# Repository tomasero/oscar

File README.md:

#Oscar
####Interactive Trashcan

---

###Sensors
- Infrared distance sensor
- Passive infrared sensor (motion detection)

###Actuators
- LEDs
- Sound

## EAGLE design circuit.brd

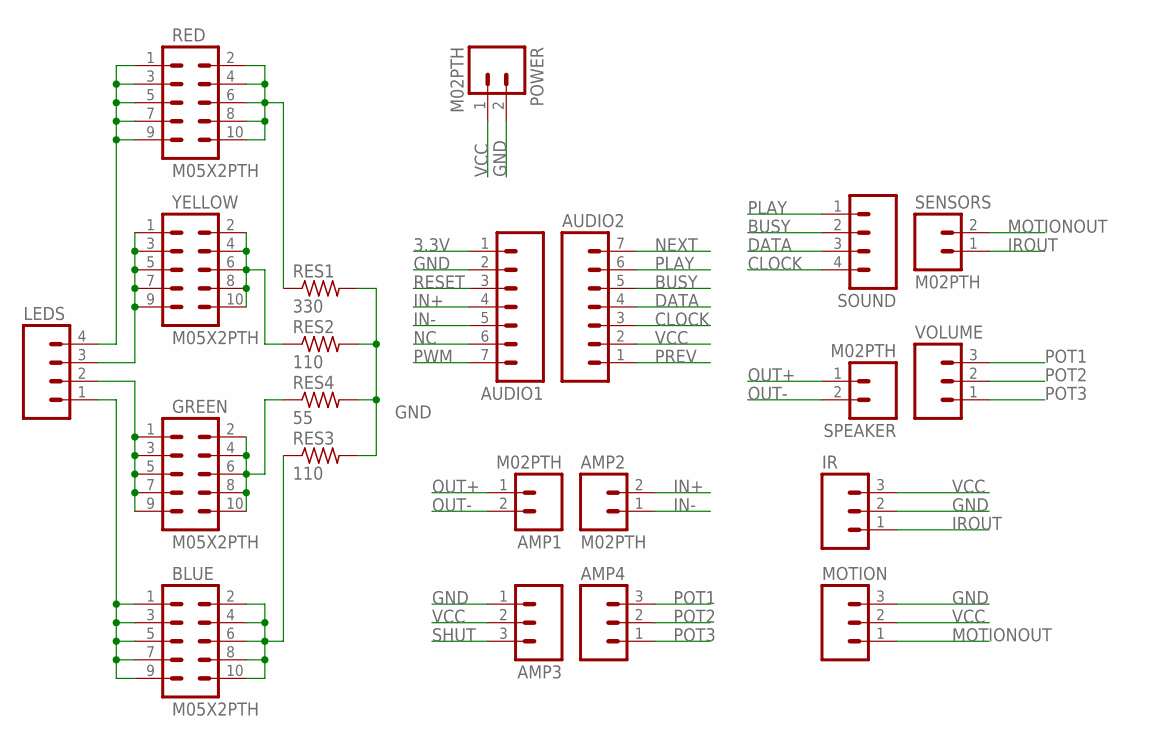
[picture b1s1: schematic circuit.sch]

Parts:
AMP1, AMP2: M02PTH; 1X02
AMP3, AMP4: M03PTH; 1X03
AUDIO1, AUDIO2: M07; 1X07
BLUE: M05X2PTH; AVR_ICSP
GREEN: M05X2PTH; AVR_ICSP
IR: M03PTH; 1X03
LEDS: M04PTH; 1X04
MOTION: M03PTH; 1X03
POWER: M02PTH; 1X02
RED: M05X2PTH; AVR_ICSP
RES1: 330; 0204V
RES2, RES3: 110; 0204V
RES4: 55; 0204V
SENSORS: M02PTH; 1X02
SOUND: M04PTH; 1X04
SPEAKER: M02PTH; 1X02
VOLUME: M03PTH; 1X03
YELLOW: M05X2PTH; AVR_ICSP

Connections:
3.3V: AUDIO1.1
BUSY: AUDIO2.5, SOUND.2
CLOCK: AUDIO2.3, SOUND.4
DATA: AUDIO2.4, SOUND.3
GND: AMP3.1, AUDIO1.2, IR.2, MOTION.3, POWER.2, RES1.2, RES2.2, RES3.2, RES4.2
IN+: AMP2.2, AUDIO1.4
IN-: AMP2.1, AUDIO1.5
IROUT: IR.1, SENSORS.1
MOTIONOUT: MOTION.1, SENSORS.2
unnamed: LEDS.4, RED.1, RED.3, RED.5, RED.7, RED.9
unnamed: LEDS.3, YELLOW.1, YELLOW.3, YELLOW.5, YELLOW.7, YELLOW.9
unnamed: GREEN.1, GREEN.3, GREEN.5, GREEN.7, GREEN.9, LEDS.2
unnamed: BLUE.1, BLUE.3, BLUE.5, BLUE.7, BLUE.9, LEDS.1
unnamed: RED.2, RED.4, RED.6, RED.8, RED.10, RES1.1
unnamed: RES2.1, YELLOW.2, YELLOW.4, YELLOW.6, YELLOW.8, YELLOW.10
unnamed: GREEN.2, GREEN.4, GREEN.6, GREEN.8, GREEN.10, RES4.1
unnamed: BLUE.2, BLUE.4, BLUE.6, BLUE.8, BLUE.10, RES3.1
NC: AUDIO1.6
NEXT: AUDIO2.7
OUT+: AMP1.1, SPEAKER.1
OUT-: AMP1.2, SPEAKER.2
PLAY: AUDIO2.6, SOUND.1
POT1: AMP4.3, VOLUME.3
POT2: AMP4.2, VOLUME.2
POT3: AMP4.1, VOLUME.1
PREV: AUDIO2.1
PWM: AUDIO1.7
RESET: AUDIO1.3
SHUT: AMP3.3
VCC: AMP3.2, AUDIO2.2, IR.3, MOTION.2, POWER.1

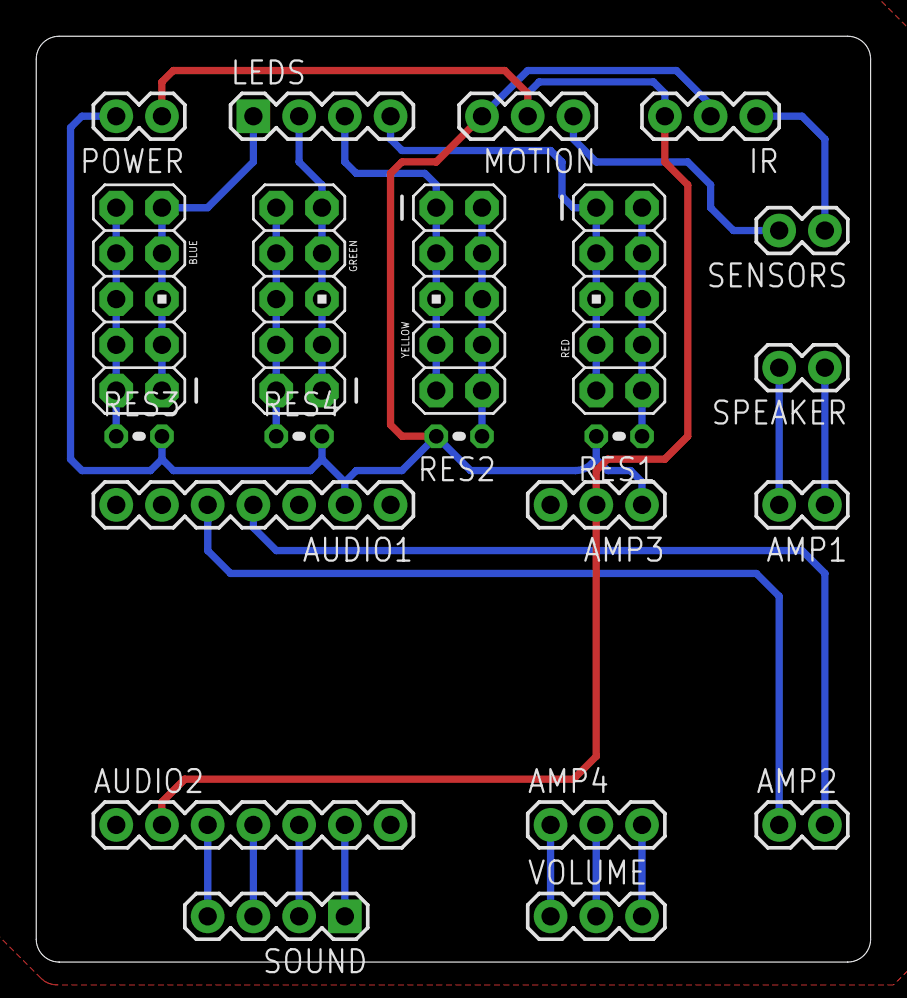
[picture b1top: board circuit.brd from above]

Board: 2 copper layers, 46.4 x 51.4 mm, 22 parts (0 on the bottom side), 23 nets.

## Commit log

2015-02-10 added ir and ms
2015-02-10 added img and readme
2015-02-10 added imgs and readme
2015-02-11 add LED controlling program
2015-02-11 added sound code into led code
2015-02-11 deleted unnecessary file
2015-02-11 works!
2015-02-12 adding wav files
2015-02-16 Adding Oscar trash can sounds
2015-02-17 updating everything
2015-02-17 latest changes
2015-02-18 clean up code
2015-02-19 trying to pull
2015-02-19 code cleanup

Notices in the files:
parts and their libraries:
SparkFun-Connectors: Licensing: Creative Commons ShareAlike 4.0 International - https://creativecommons.org/licenses/by-sa/4.0
